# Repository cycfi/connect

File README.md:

# connect
Peripherals for connecting and controlling musical instruments

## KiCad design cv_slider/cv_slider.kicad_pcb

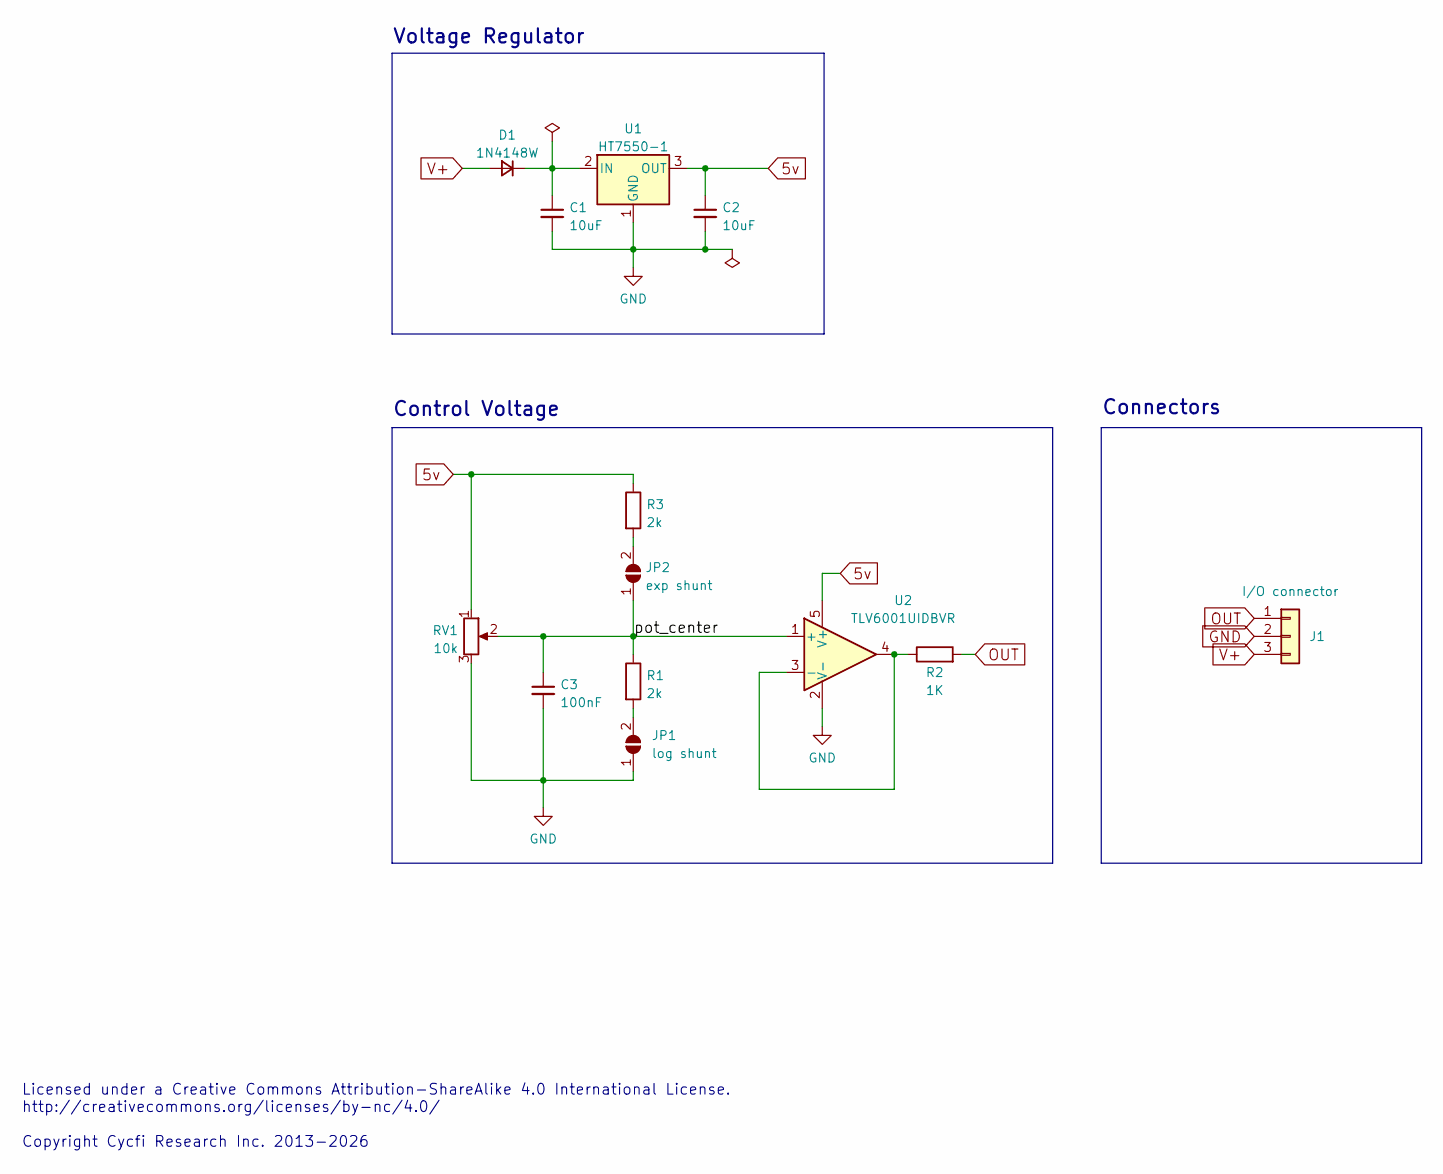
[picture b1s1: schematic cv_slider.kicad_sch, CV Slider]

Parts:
C1, C2: 10uF; C_0805_2012Metric; LCSC C15850
C3: 100nF; C_0402_1005Metric; LCSC C307331
D1: 1N4148W; D_SOD-123; LCSC C81598
J1: I/O connector; pin_header_1x3p_2.54mm_smd_horizontal; LCSC C5242196
JP1: log shunt; SolderJumper-2_P1.3mm_Open_TrianglePad1.0x1.5mm
JP2: exp shunt; SolderJumper-2_P1.3mm_Open_TrianglePad1.0x1.5mm
R1, R3: 2k; R_0402_1005Metric; LCSC C4109
R2: 1K; R_0402_1005Metric; LCSC C11702
RV1: 10k; Alps_RS301111A01G
U1: HT7550-1; SOT-89-3; LCSC C16106
U2: TLV6001UIDBVR; SOT-23-5; LCSC C544299

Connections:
5v: C2.1, R3.1, RV1.1, U1.3 (OUT), U2.5 (V+)
/pot_center: C3.1, JP2.1 (A), R1.1, RV1.2, U2.1 (+)
GND: C1.2, C2.2, C3.2, J1.2, JP1.1 (A), RV1.3, U1.1 (GND), U2.2 (V-)
unnamed: C1.1, D1.1 (K), U1.2 (IN)
unnamed: JP1.2 (B), R1.2
unnamed: JP2.2 (B), R3.2
unnamed: R2.1, U2.3 (-), U2.4
OUT: J1.1, R2.2
V+: D1.2 (A), J1.3

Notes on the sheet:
Control Voltage
Licensed under a Creative Commons Attribution-ShareAlike 4.0 International License. http://creativecommons.org/licenses/by-nc/4.0/ Copyright Cycfi Research Inc. 2013-2026
Voltage Regulator
Connectors

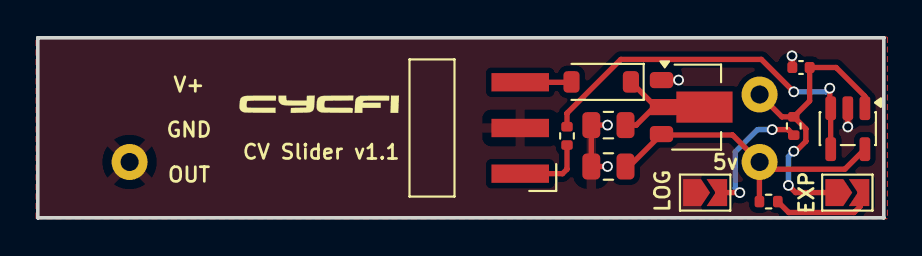
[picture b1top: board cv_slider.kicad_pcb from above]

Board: 2 copper layers, 47.0 x 10.0 mm, 13 parts (1 on the bottom side), 9 nets.

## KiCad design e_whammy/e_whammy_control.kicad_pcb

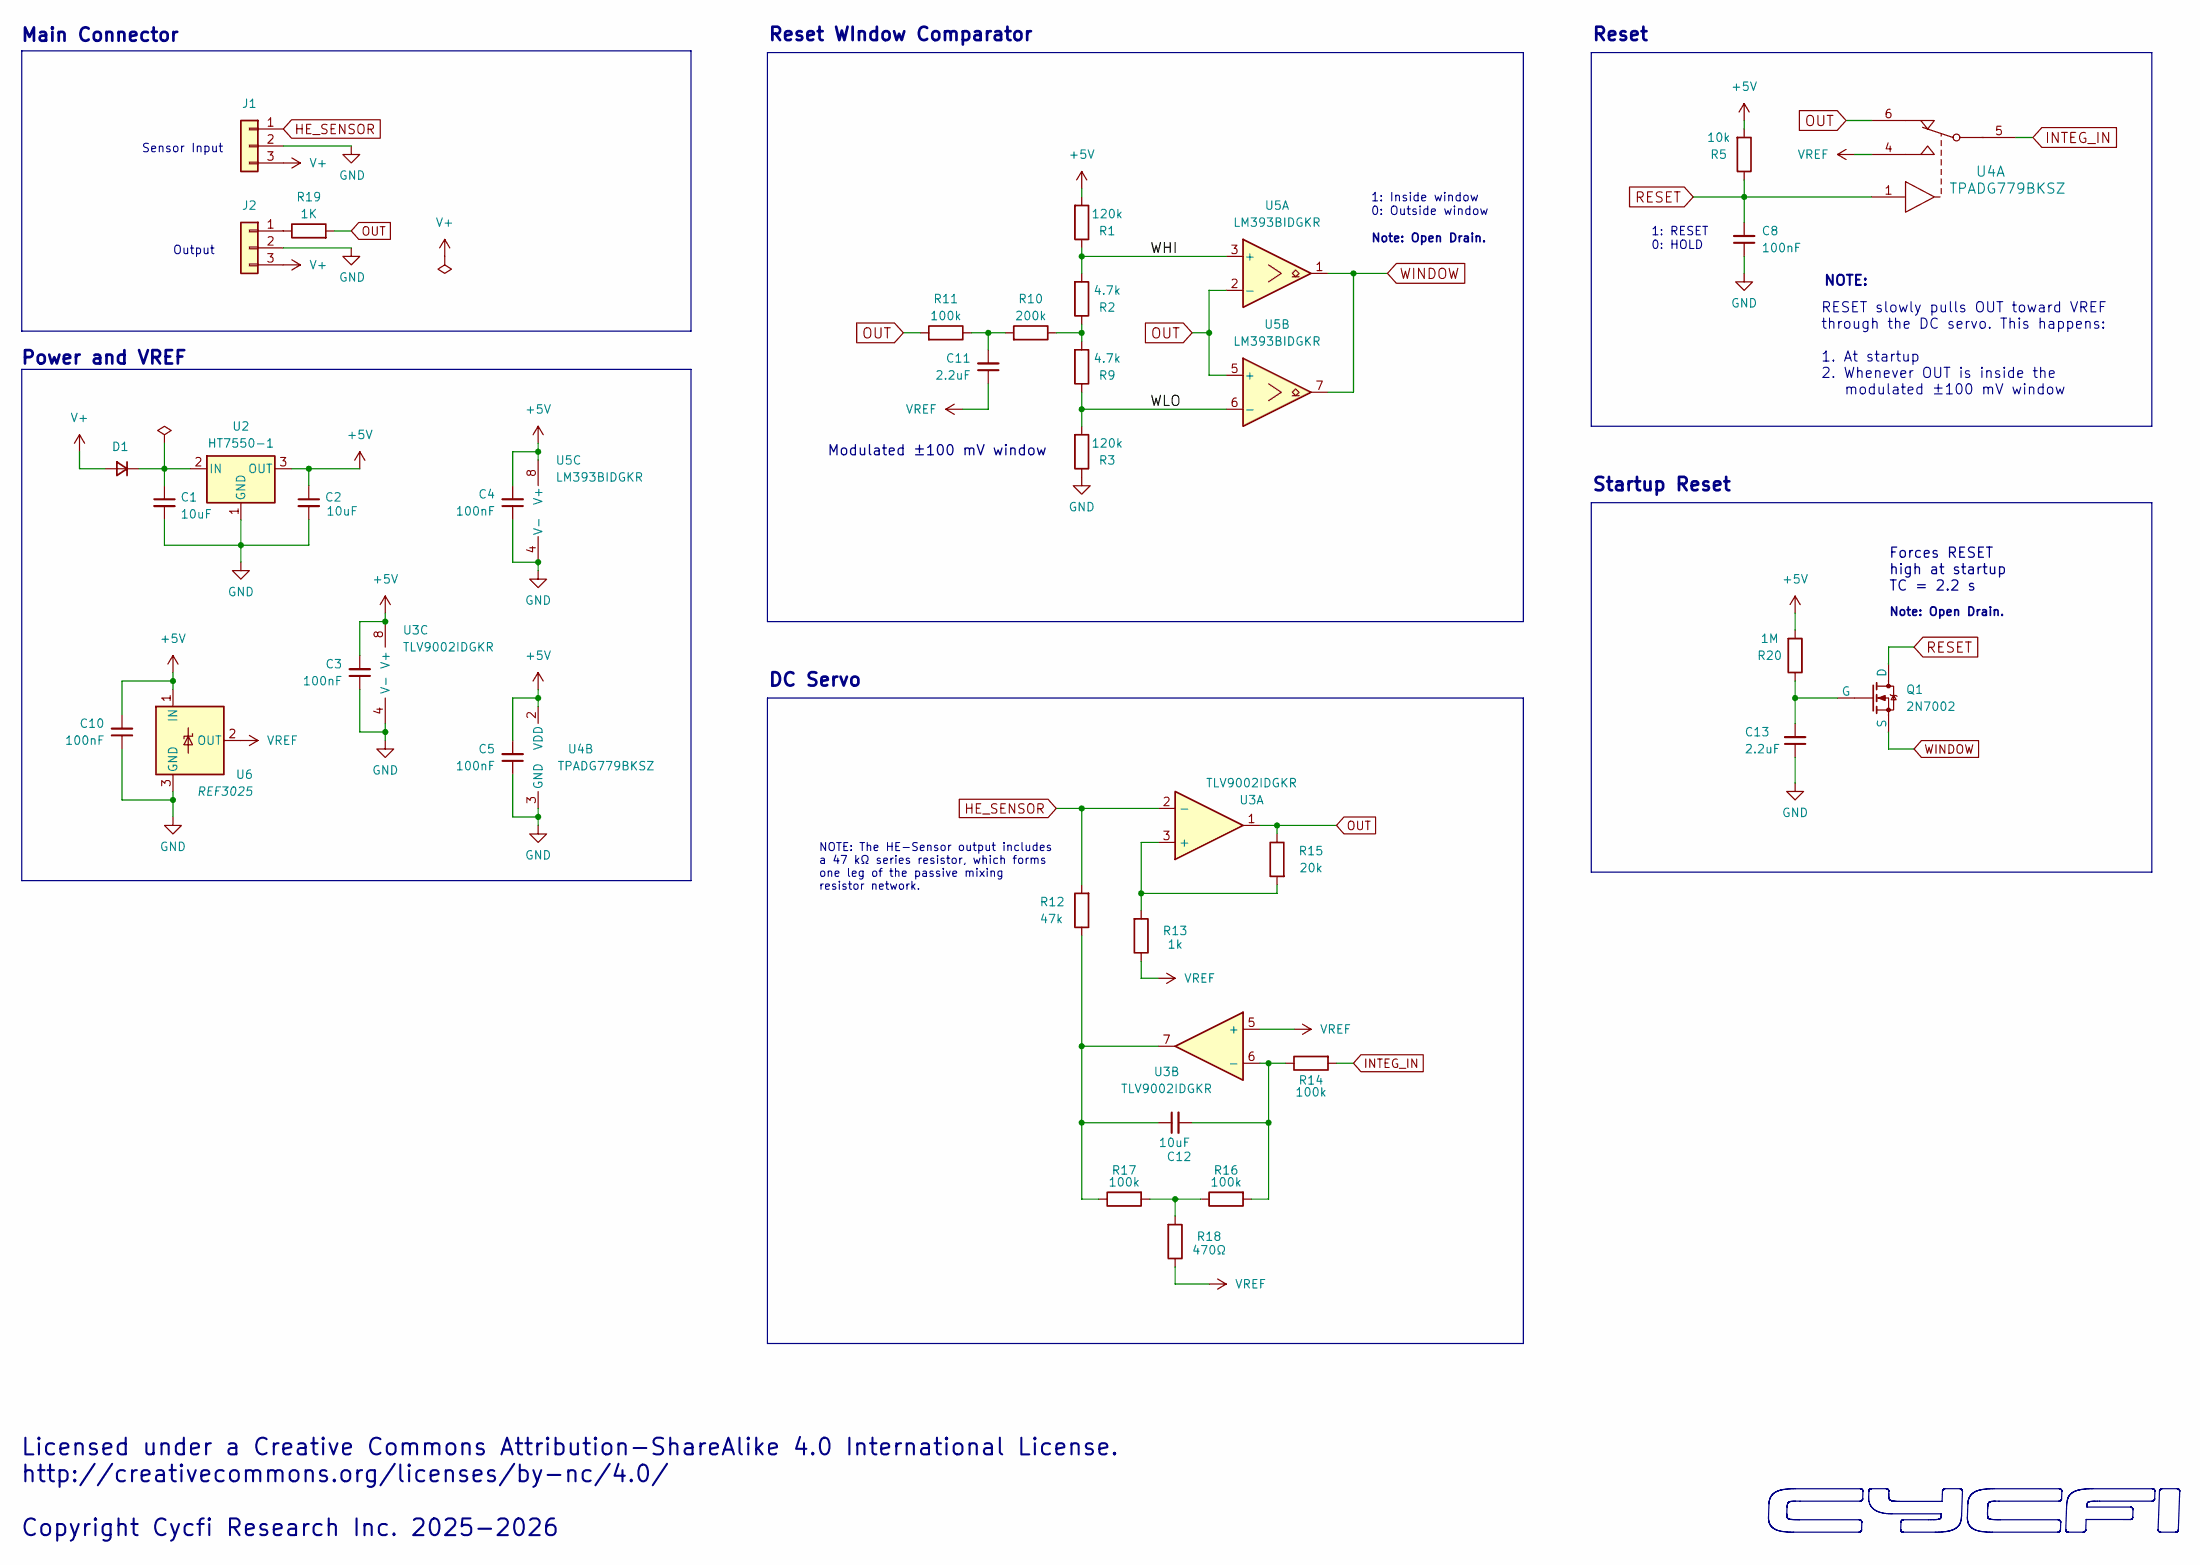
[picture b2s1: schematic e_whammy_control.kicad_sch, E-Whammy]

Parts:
C1, C2: 10uF; C_0603_1608Metric; LCSC C96446
C3, C4, C5, C8, C10: 100nF; C_0402_1005Metric; LCSC C307331
C11, C13: 2.2uF; C_0402_1005Metric; LCSC C72203
C12: 10uF; C_0805_2012Metric; LCSC C95841
D1: 1N4148WS; D_SOD-323; LCSC C2128
J1, J2: Conn_01x03; pin_header_1x3p_2.54mm_smd_horizontal
Q1: 2N7002; SOT-23; LCSC C8545
R1, R3: 120k; R_0402_1005Metric; LCSC C25750
R2, R9: 4.7k; R_0402_1005Metric; LCSC C25900
R5: 10k; R_0402_1005Metric; LCSC C25744
R10: 200k; R_0402_1005Metric; LCSC C25764
R11: 100k; R_0402_1005Metric; LCSC C25741
R12: 47k; R_0402_1005Metric; LCSC C25792
R13: 1k; R_0402_1005Metric; LCSC C11702
R14, R16, R17: 100k; R_0402_1005Metric; LCSC C25530
R15: 20k; R_0402_1005Metric; LCSC C25765
R18: 470Ω; R_0402_1005Metric; LCSC C25117
R19: 1K; R_0402_1005Metric; LCSC C11702
R20: 1M; R_0402_1005Metric; LCSC C26083
U2: HT7550-1; SOT-23-132; LCSC C5379082
U3: TLV9002IDGKR; VSSOP-8_3x3mm_P0.65mm; LCSC C398361
U4: TPADG779BKSZ; KS_6_ADI; LCSC C42449021
U5: LM393BIDGKR; VSSOP-8_3x3mm_P0.65mm; LCSC C3659248
U6: REF3025; SOT-23; LCSC C11334

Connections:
+5V: C2.1, C3.2, C4.2, C5.2, C10.2, R1.2, R5.2, R20.2, U2.3 (OUT), U3.8 (V+), U4.2 (VDD), U5.8 (V+), U6.1 (IN)
/WHI: R1.1, R2.2, U5.3 (+)
/WLO: R3.2, R9.1, U5.6 (-)
GND: C1.2, C2.2, C3.1, C4.1, C5.1, C8.1, C10.1, C13.1, J1.2, J2.2, R3.1, U2.1 (GND), U3.4 (V-), U4.3 (GND), U5.4 (V-), U6.3 (GND)
HE_SENSOR: J1.1, R12.2, U3.2 (-)
INTEG_IN: R14.2, U4.5
unnamed: C11.2, R10.2, R11.1
unnamed: C12.1, R12.1, R17.1, U3.7
unnamed: C1.1, D1.1 (K), U2.2 (IN)
unnamed: J2.1, R19.1
unnamed: C13.2, Q1.1 (G), R20.1
unnamed: R2.1, R9.2, R10.1
unnamed: R16.1, R17.2, R18.2
unnamed: R13.2, R15.2, U3.3 (+)
unnamed: C12.2, R14.1, R16.2, U3.6 (-)
OUT: R11.2, R15.1, R19.2, U3.1, U4.6, U5.2 (-), U5.5 (+)
RESET: C8.2, Q1.3 (D), R5.1, U4.1
V+: D1.2 (A), J1.3, J2.3
VREF: C11.1, R13.1, R18.1, U3.5 (+), U4.4, U6.2 (OUT)
WINDOW: Q1.2 (S), U5.1, U5.7

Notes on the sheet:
Modulated ±100 mV window
NOTE:
Reset
Main Connector
Note: Open Drain.
NOTE: The HE-Sensor output includes a 47 kΩ series resistor, which forms one leg of the passive mixing resistor network.
Sensor Input
DC Servo
RESET slowly pulls OUT toward VREF through the DC servo. This happens: 1. At startup 2. Whenever OUT is inside the modulated ±100 mV window
1: RESET 0: HOLD
Output
Reset WIndow Comparator
Startup Reset
Licensed under a Creative Commons Attribution-ShareAlike 4.0 International License. http://creativecommons.org/licenses/by-nc/4.0/ Copyright Cycfi Research Inc. 2025-2026
Forces RESET high at startup TC = 2.2 s
1: Inside window 0: Outside window
Power and VREF

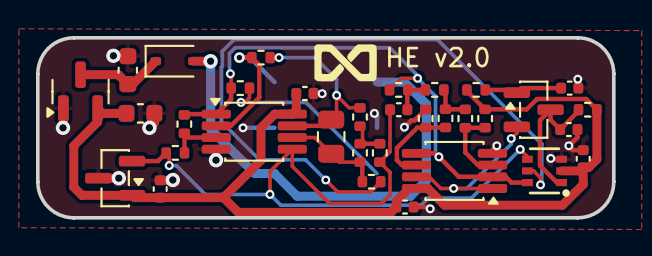
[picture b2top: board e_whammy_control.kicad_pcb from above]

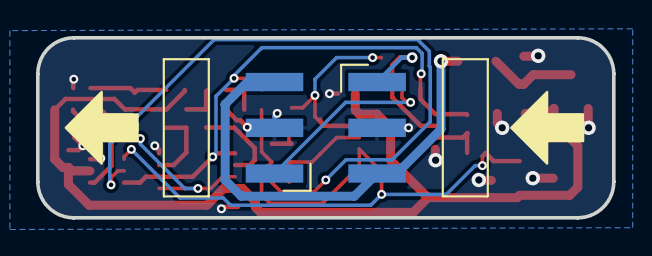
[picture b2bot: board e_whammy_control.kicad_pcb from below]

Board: 2 copper layers, 32.0 x 10.0 mm, 35 parts (2 on the bottom side), 20 nets.

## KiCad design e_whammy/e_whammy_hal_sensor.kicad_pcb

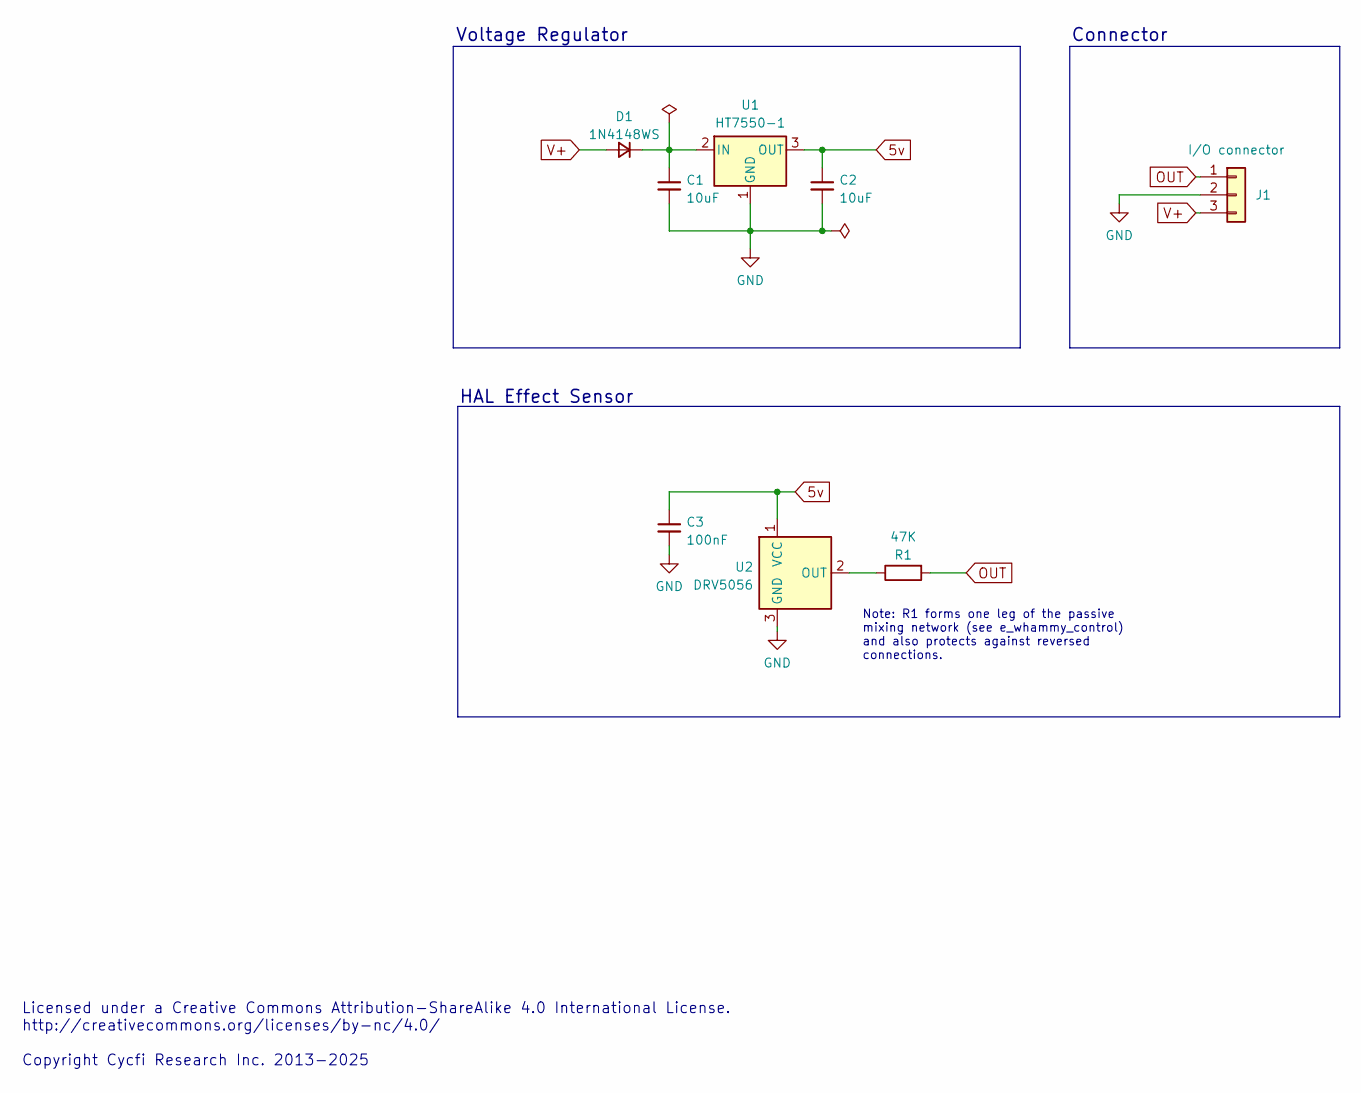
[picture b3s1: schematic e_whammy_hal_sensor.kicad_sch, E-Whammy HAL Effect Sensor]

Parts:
C1, C2: 10uF; C_0603_1608Metric; LCSC C96446
C3: 100nF; C_0402_1005Metric; LCSC C307331
D1: 1N4148WS; D_SOD-323; LCSC C2128
J1: I/O connector; PinHeader_1x03_P2.54mm_Vertical; LCSC C6332196
R1: 47K; R_0402_1005Metric; LCSC C25792
U1: HT7550-1; SOT-23-132; LCSC C5379082
U2: DRV5056; SOT-23; LCSC C2866615

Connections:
5v: C2.1, C3.1, U1.3 (OUT), U2.1 (VCC)
GND: C1.2, C2.2, C3.2, J1.2, U1.1 (GND), U2.3 (GND)
unnamed: C1.1, D1.1 (K), U1.2 (IN)
unnamed: R1.1, U2.2 (OUT)
OUT: J1.1, R1.2
V+: D1.2 (A), J1.3

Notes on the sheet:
Note: R1 forms one leg of the passive mixing network (see e_whammy_control) and also protects against reversed connections.
Connector
Licensed under a Creative Commons Attribution-ShareAlike 4.0 International License. http://creativecommons.org/licenses/by-nc/4.0/ Copyright Cycfi Research Inc. 2013-2025
Voltage Regulator
HAL Effect Sensor

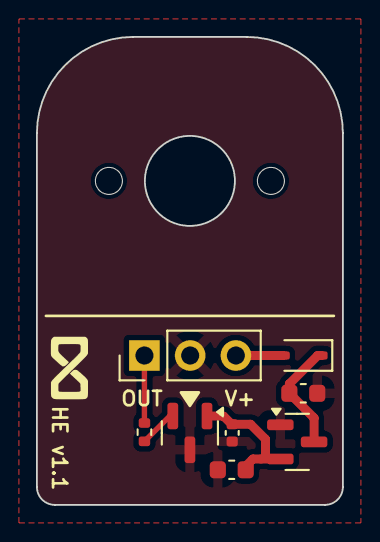
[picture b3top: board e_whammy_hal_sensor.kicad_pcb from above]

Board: 2 copper layers, 17.0 x 26.0 mm, 8 parts (0 on the bottom side), 6 nets.

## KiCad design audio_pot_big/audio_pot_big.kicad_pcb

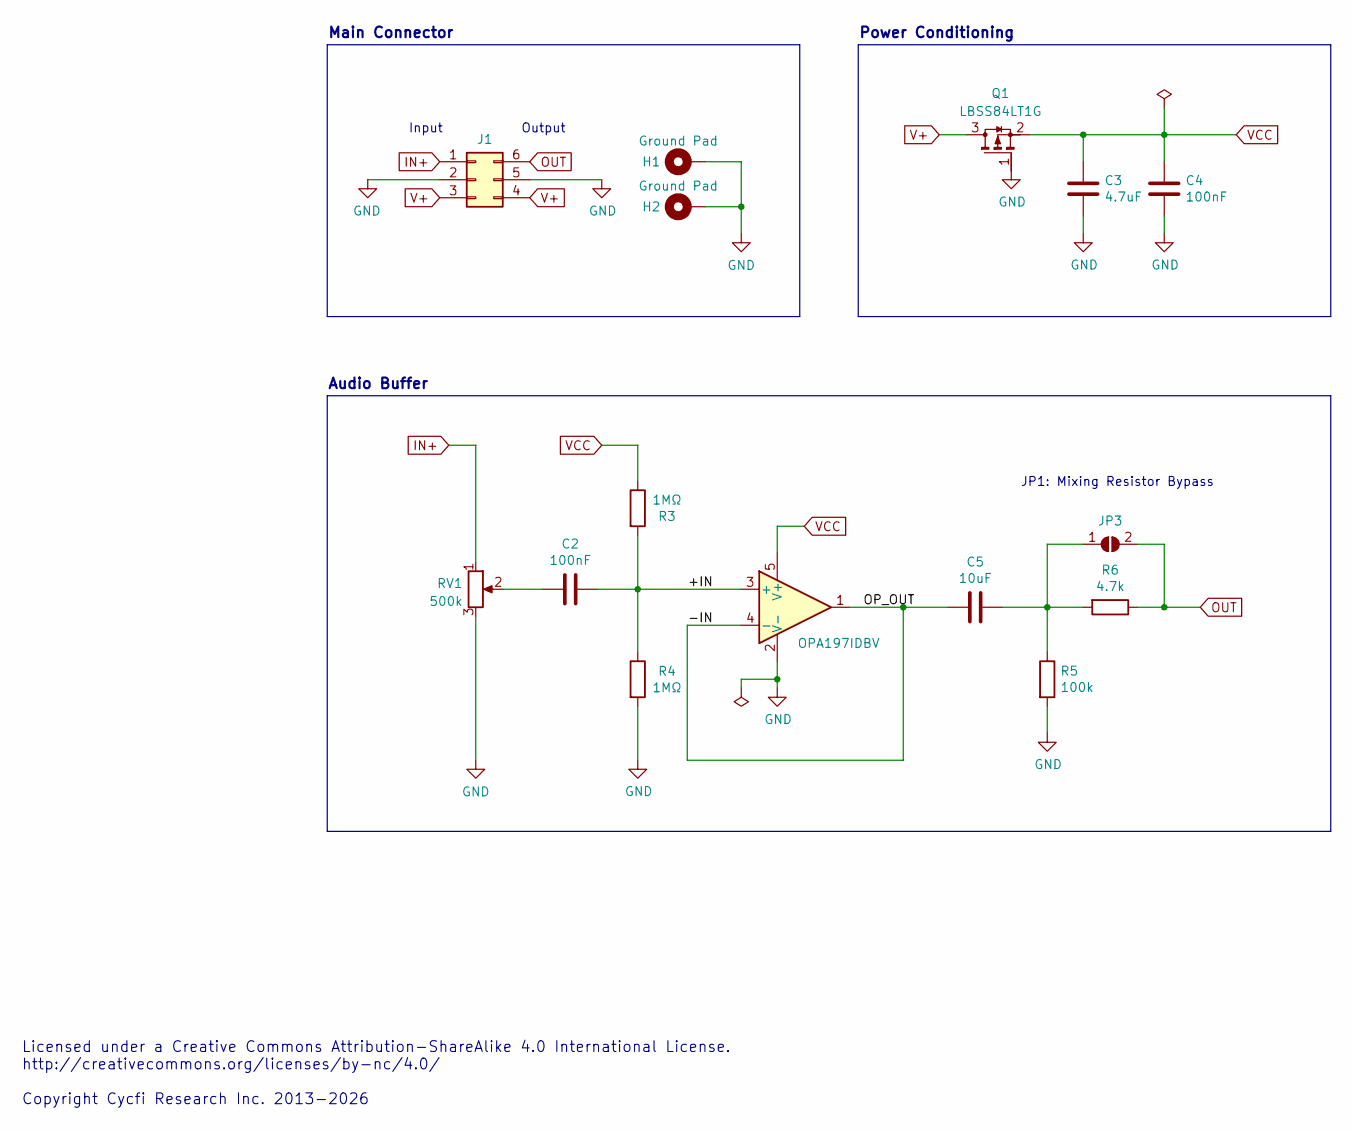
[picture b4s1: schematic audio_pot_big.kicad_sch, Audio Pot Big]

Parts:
C2: 100nF; C_0805_2012Metric; LCSC C49678
C3: 4.7uF; C_0805_2012Metric; LCSC C1779
C4: 100nF; C_0402_1005Metric; LCSC C307331
C5: 10uF; C_0805_2012Metric; LCSC C15850
H1, H2: Ground Pad; single-pad-2x2-circular
J1: Conn_02x03_Counter_Clockwise; pin_header_2x3p_2.54mm_smd_horizontal; LCSC C46061685
JP3: SolderJumper_2_Open; SolderJumper-2_P1.3mm_Open_TrianglePad1.0x1.5mm
Q1: LBSS84LT1G; TSOT-23; LCSC C8492
R3, R4: 1MΩ; R_0402_1005Metric; LCSC C26083
R5: 100k; R_0402_1005Metric; LCSC C25741
R6: 4.7k; R_0402_1005Metric; LCSC C25900
RV1: 500k; bourns_pdb241
U1: OPA197IDBV; SOT-23-5; LCSC C131929

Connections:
/+IN: C2.1, R3.2, R4.1, U1.3 (+)
/-IN: C5.2, U1.1, U1.4 (-)
GND: C3.2, C4.2, H1.1, H2.1, J1.2, J1.5, Q1.1 (G), R4.2, R5.2, RV1.3, U1.2 (V-)
IN+: J1.1, RV1.1
unnamed: C2.2, RV1.2
unnamed: C5.1, JP3.1 (A), R5.1, R6.2
OUT: J1.6, JP3.2 (B), R6.1
V+: J1.3, J1.4, Q1.3 (D)
VCC: C3.1, C4.1, Q1.2 (S), R3.1, U1.5 (V+)

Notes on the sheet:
Power Conditioning
JP1: Mixing Resistor Bypass
Input
Licensed under a Creative Commons Attribution-ShareAlike 4.0 International License. http://creativecommons.org/licenses/by-nc/4.0/ Copyright Cycfi Research Inc. 2013-2026
Output
Main Connector
Audio Buffer

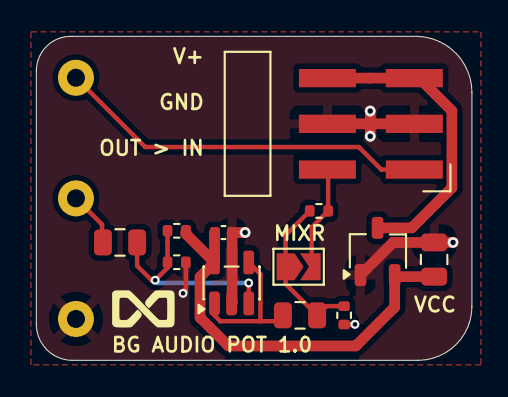
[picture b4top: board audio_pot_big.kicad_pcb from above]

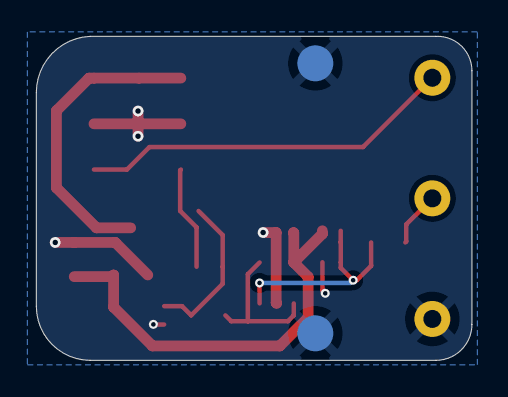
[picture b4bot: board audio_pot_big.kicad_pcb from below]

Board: 2 copper layers, 24.2 x 18.0 mm, 15 parts (2 on the bottom side), 9 nets.

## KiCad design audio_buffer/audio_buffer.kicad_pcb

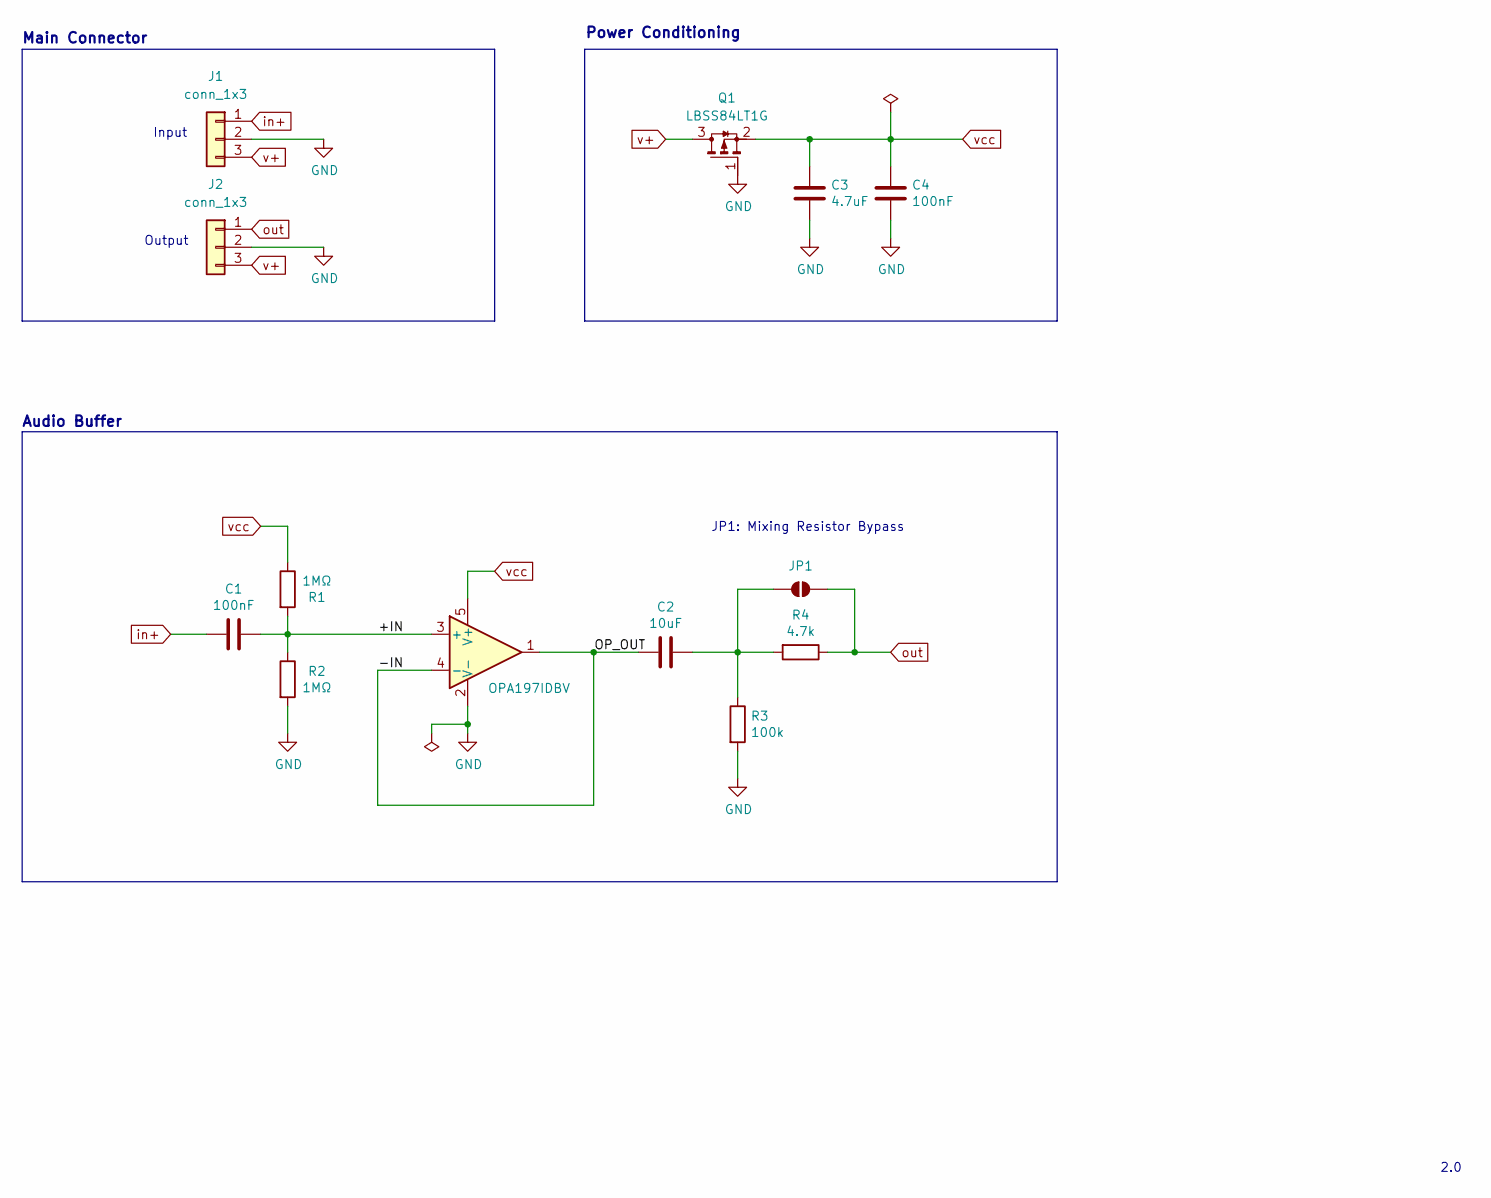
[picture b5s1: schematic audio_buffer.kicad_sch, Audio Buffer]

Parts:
C1: 100nF; C_0805_2012Metric; LCSC C49678
C2: 10uF; C_0805_2012Metric; LCSC C15850
C3: 4.7uF; C_0805_2012Metric; LCSC C1779
C4: 100nF; C_0402_1005Metric; LCSC C307331
J1, J2: conn_1x3; pin_header_1x3p_2.54mm_smd_horizontal
JP1: SolderJumper_2_Open; SolderJumper-2_P1.3mm_Open_TrianglePad1.0x1.5mm
Q1: LBSS84LT1G; TSOT-23; LCSC C8492
R1, R2: 1MΩ; R_0402_1005Metric; LCSC C26083
R3: 100k; R_0402_1005Metric; LCSC C25741
R4: 4.7k; R_0402_1005Metric; LCSC C25900
U1: OPA197IDBV; SOT-23-5; LCSC C131929

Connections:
/+IN: C1.1, R1.2, R2.1, U1.3 (+)
/-IN: C2.2, U1.1, U1.4 (-)
GND: C3.2, C4.2, J1.2, J2.2, Q1.1 (G), R2.2, R3.2, U1.2 (V-)
unnamed: C2.1, JP1.1 (A), R3.1, R4.2
in+: C1.2, J1.1
out: J2.1, JP1.2 (B), R4.1
v+: J1.3, J2.3, Q1.3 (D)
vcc: C3.1, C4.1, Q1.2 (S), R1.1, U1.5 (V+)

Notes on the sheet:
Power Conditioning
Input
JP1: Mixing Resistor Bypass
2.0
Output
Audio Buffer
Main Connector

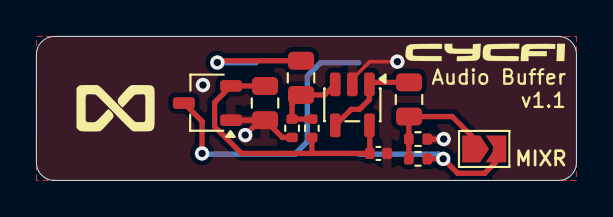
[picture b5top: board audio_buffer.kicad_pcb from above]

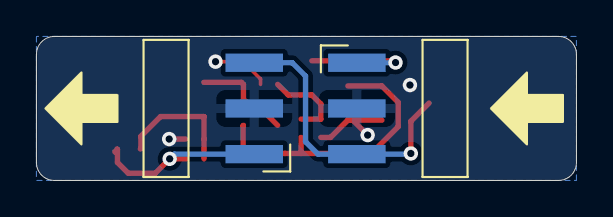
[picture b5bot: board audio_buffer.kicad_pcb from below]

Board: 2 copper layers, 30.0 x 8.0 mm, 13 parts (2 on the bottom side), 8 nets.

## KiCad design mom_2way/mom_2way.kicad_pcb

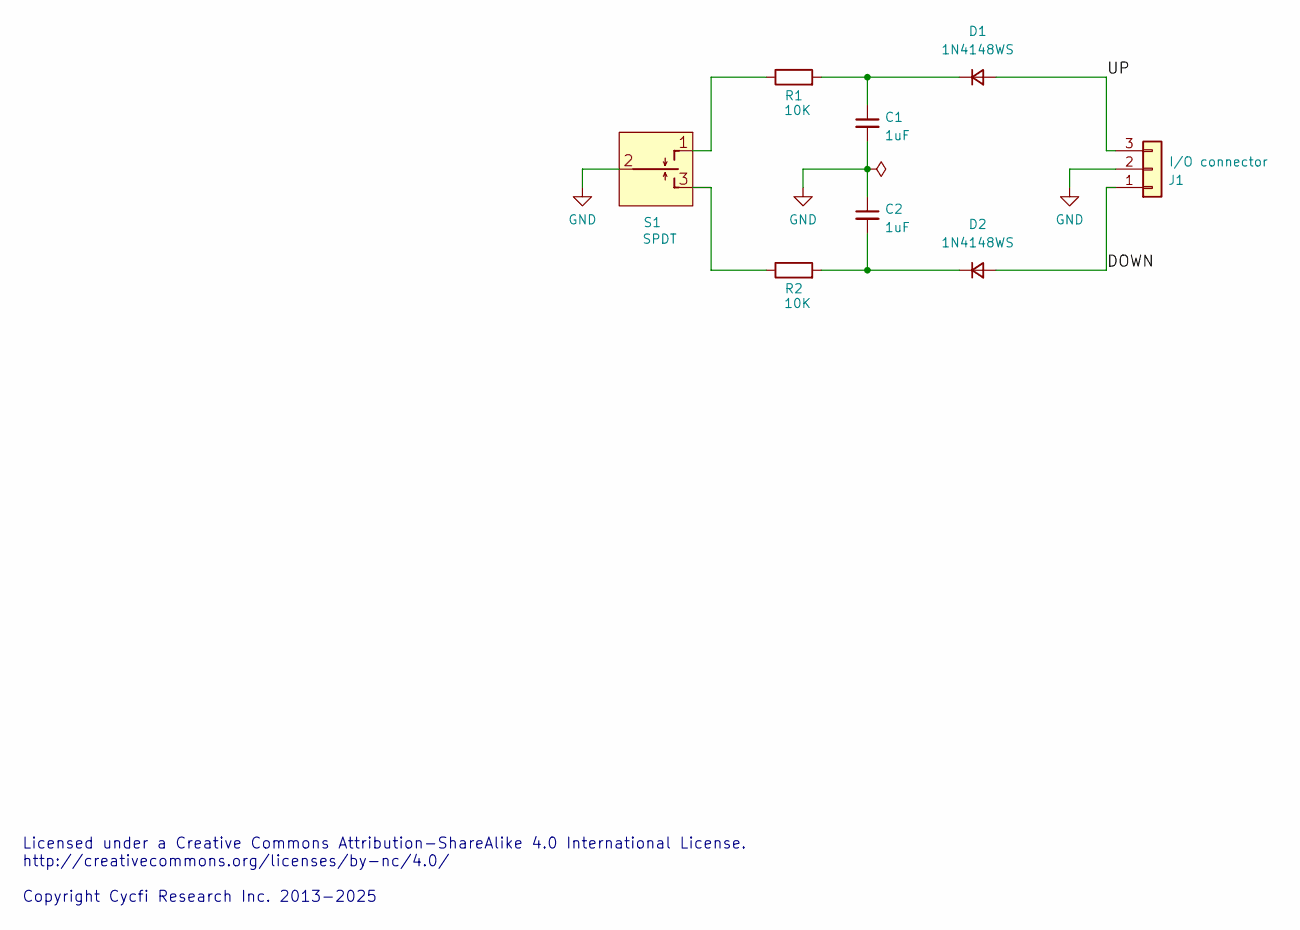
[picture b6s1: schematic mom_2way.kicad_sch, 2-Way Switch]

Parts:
C1, C2: 1uF; C_0603_1608Metric; LCSC C15849
D1, D2: 1N4148WS; D_SOD-323; LCSC C2128
J1: I/O connector; pin_header_1x3p_2.54mm_smd_horizontal; LCSC C6332196
R1, R2: 10K; R_0402_1005Metric; LCSC C25744
S1: SPDT; MINI_SPDT

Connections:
/DOWN: D2.2 (A), J1.1
/UP: D1.2 (A), J1.3
GND: C1.2, C2.1, J1.2, S1.2
unnamed: C1.1, D1.1 (K), R1.2
unnamed: C2.2, D2.1 (K), R2.2
unnamed: R1.1, S1.1 (O)
unnamed: R2.1, S1.3 (S)

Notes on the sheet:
Licensed under a Creative Commons Attribution-ShareAlike 4.0 International License. http://creativecommons.org/licenses/by-nc/4.0/ Copyright Cycfi Research Inc. 2013-2025

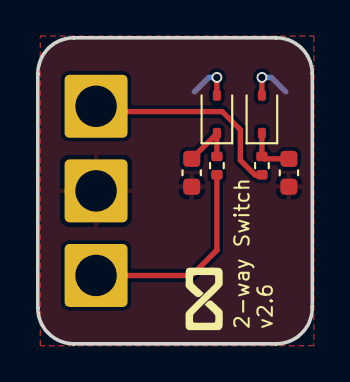
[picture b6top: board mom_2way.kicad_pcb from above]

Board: 2 copper layers, 15.2 x 17.0 mm, 8 parts (1 on the bottom side), 7 nets.

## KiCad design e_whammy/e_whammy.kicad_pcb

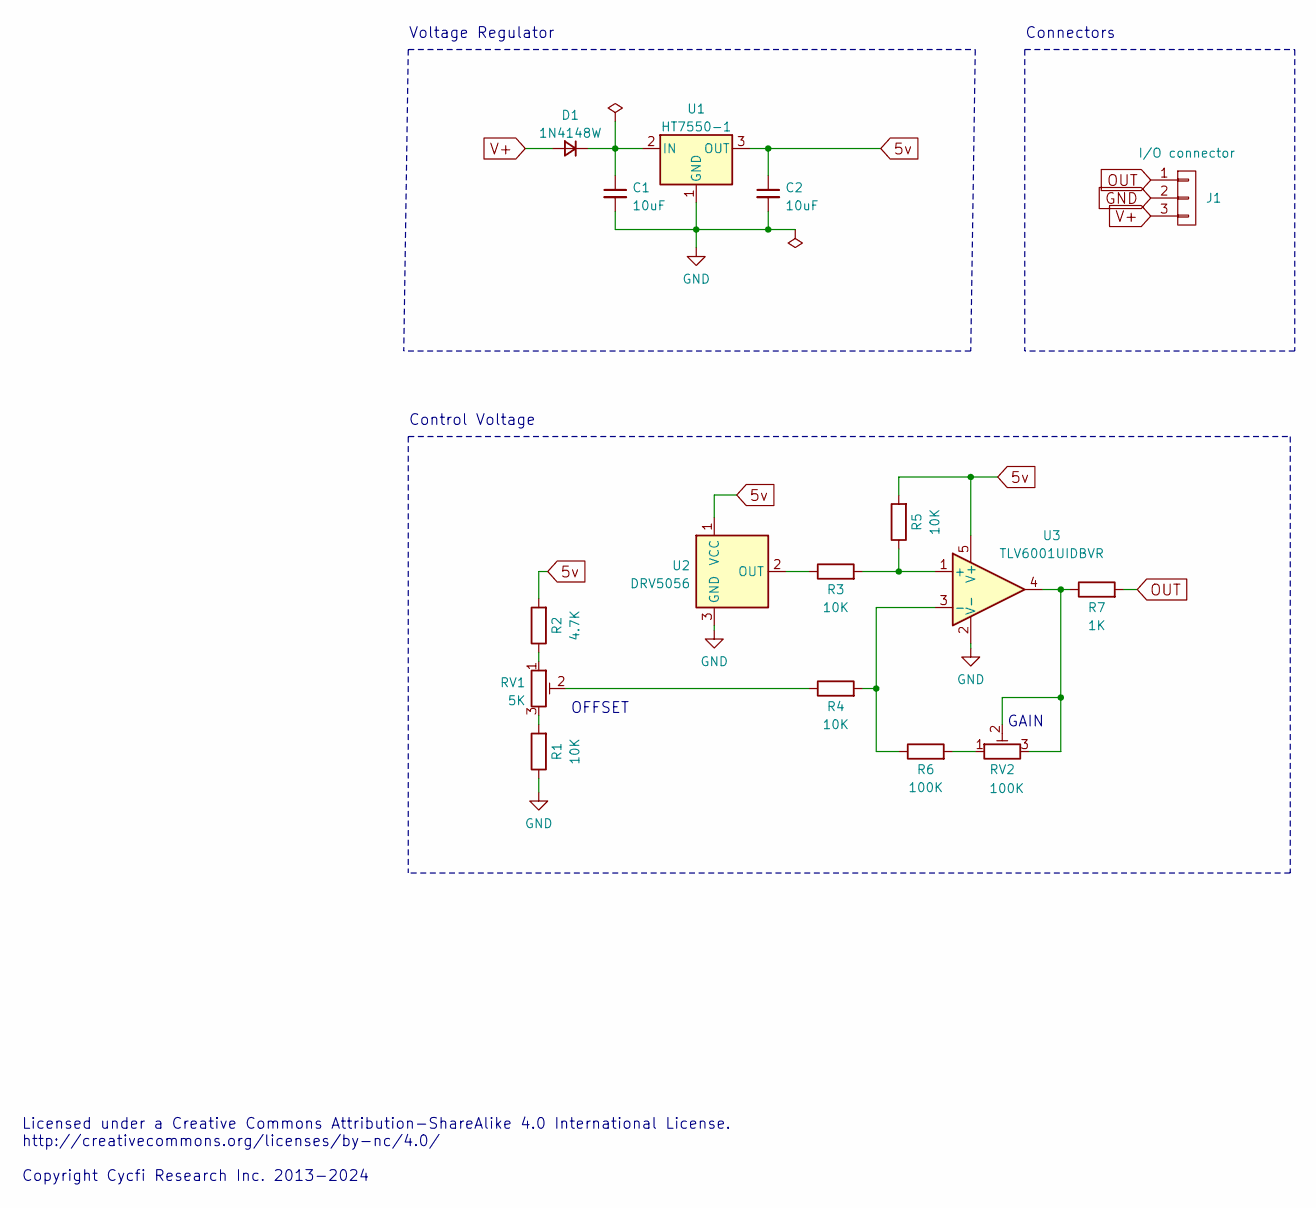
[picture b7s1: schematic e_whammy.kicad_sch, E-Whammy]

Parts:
C1, C2: 10uF; C_0805_2012Metric; LCSC C15850
D1: 1N4148W; D_SOD-123; LCSC C81598
J1: I/O connector; PinHeader_1x03_P2.54mm_Vertical; LCSC C6332196
R1, R3, R4, R5: 10K; R_0402_1005Metric; LCSC C25744
R2: 4.7K; R_0402_1005Metric; LCSC C25900
R6: 100K; R_0402_1005Metric; LCSC C25741
R7: 1K; R_0402_1005Metric; LCSC C11702
RV1: 5K; TC33X-2; LCSC C719177
RV2: 100K; TC33X-2; LCSC C719186
U1: HT7550-1; SOT-89-3; LCSC C16106
U2: DRV5056; SOT-23; LCSC C2866615
U3: TLV6001UIDBVR; SOT-23-5; LCSC C544299

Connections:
5v: C2.1, R2.2, R5.2, U1.3 (OUT), U2.1 (VCC), U3.5 (V+)
GND: C1.2, C2.2, J1.2, R1.1, U1.1 (GND), U2.3 (GND), U3.2 (V-)
unnamed: C1.1, D1.1 (K), U1.2 (IN)
unnamed: R1.2, RV1.3
unnamed: R2.1, RV1.1
unnamed: R4.1, RV1.2
unnamed: R6.2, RV2.1
unnamed: R7.1, RV2.2, RV2.3, U3.4
unnamed: R3.1, U2.2 (OUT)
unnamed: R3.2, R5.1, U3.1 (+)
unnamed: R4.2, R6.1, U3.3 (-)
OUT: J1.1, R7.2
V+: D1.2 (A), J1.3

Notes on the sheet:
Connectors
GAIN
OFFSET
Licensed under a Creative Commons Attribution-ShareAlike 4.0 International License. http://creativecommons.org/licenses/by-nc/4.0/ Copyright Cycfi Research Inc. 2013-2024
Voltage Regulator
Control Voltage

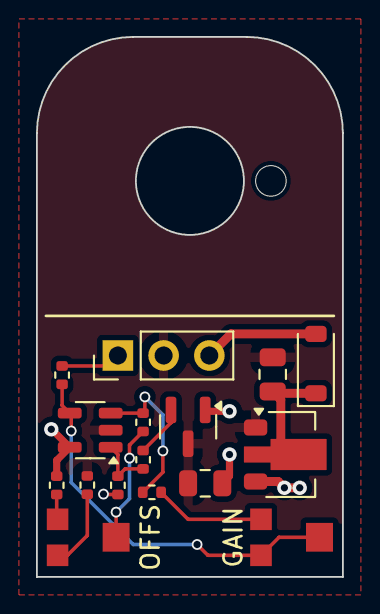
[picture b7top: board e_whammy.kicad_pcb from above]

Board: 4 copper layers, 17.0 x 30.0 mm, 16 parts (0 on the bottom side), 13 nets.

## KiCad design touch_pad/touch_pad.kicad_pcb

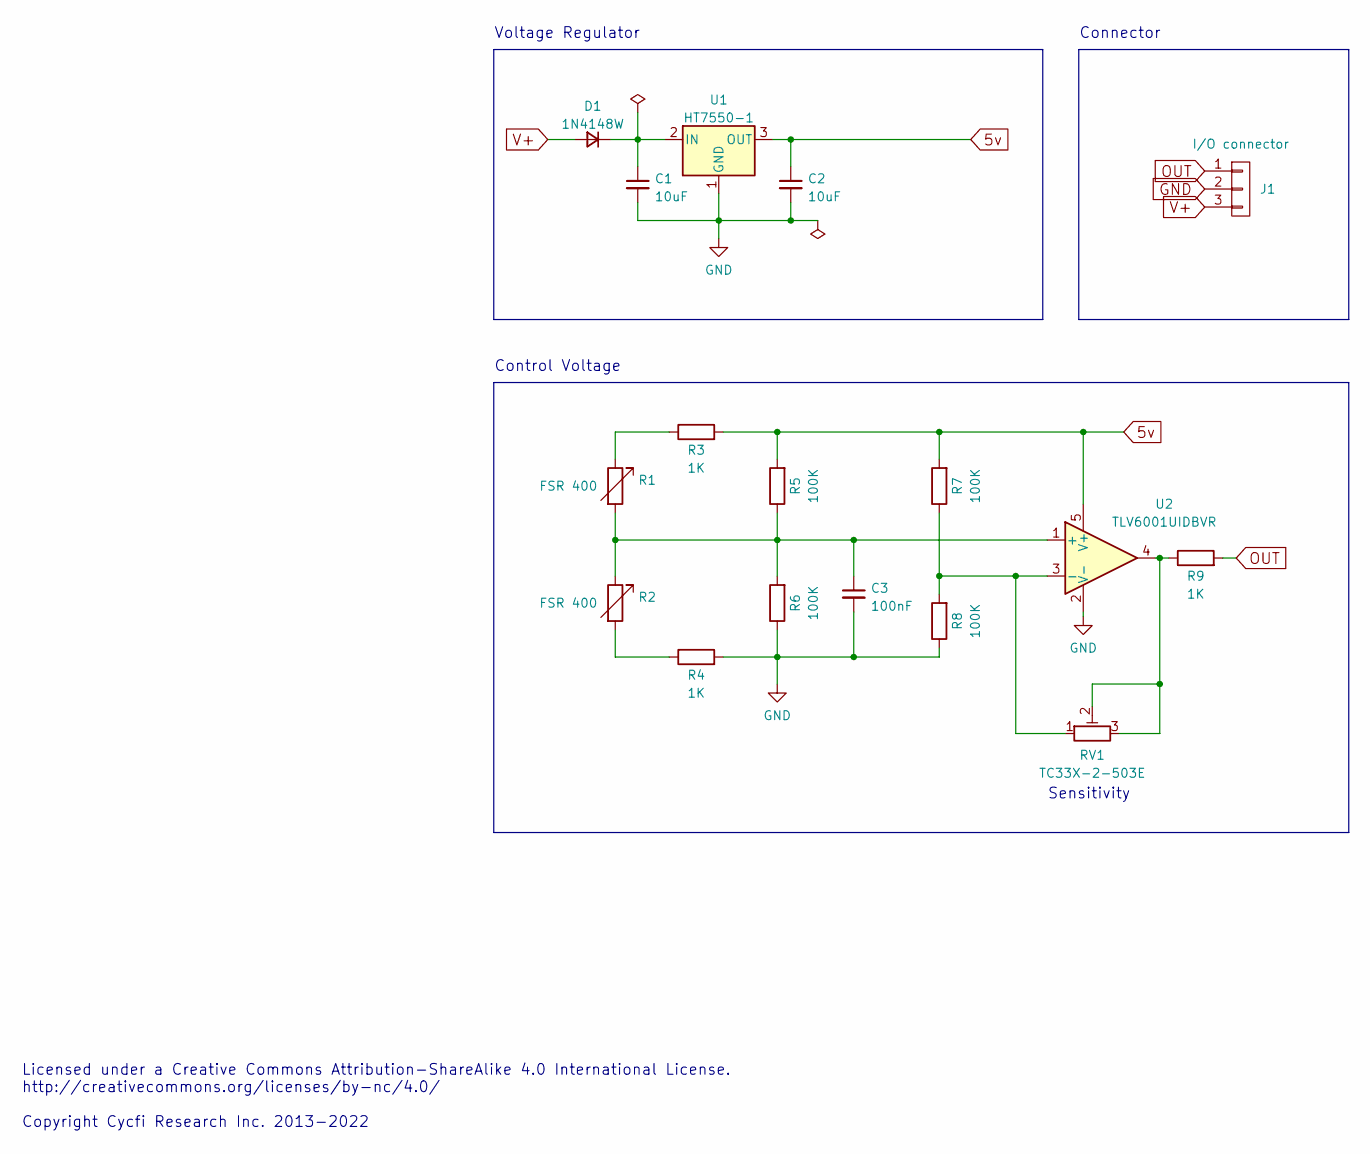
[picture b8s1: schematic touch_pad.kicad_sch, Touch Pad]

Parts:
C1, C2: 10uF; C_0805_2012Metric; LCSC C15850
C3: 100nF; C_0402_1005Metric; LCSC C307331
D1: 1N4148W; D_SOD-123; LCSC C81598
J1: I/O connector; PinHeader_1x03_P2.54mm_Vertical_SMD_Pin1Left; LCSC C2883760
R1, R2: FSR 400; FSR-400
R3, R4, R9: 1K; R_0402_1005Metric; LCSC C11702
R5, R6, R7, R8: 100K; R_0402_1005Metric; LCSC C25741
RV1: TC33X-2-503E; TC33X-2; LCSC C913246
U1: HT7550-1; SOT-89-3; LCSC C16106
U2: TLV6001UIDBVR; SOT-23-5; LCSC C544299

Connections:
5v: C2.1, R3.2, R5.2, R7.2, U1.3 (OUT), U2.5 (V+)
GND: C1.2, C2.2, C3.2, J1.2, R4.2, R6.1, R8.1, U1.1 (GND), U2.2 (V-)
unnamed: C1.1, D1.1 (K), U1.2 (IN)
unnamed: C3.1, R1.2, R2.1, R5.1, R6.2, U2.1 (+)
unnamed: R1.1, R3.1
unnamed: R2.2, R4.1
unnamed: R7.1, R8.2, RV1.1, U2.3 (-)
unnamed: R9.1, RV1.2, RV1.3, U2.4
OUT: J1.1, R9.2
V+: D1.2 (A), J1.3

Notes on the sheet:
Connector
Sensitivity
Licensed under a Creative Commons Attribution-ShareAlike 4.0 International License. http://creativecommons.org/licenses/by-nc/4.0/ Copyright Cycfi Research Inc. 2013-2022
Voltage Regulator
Control Voltage

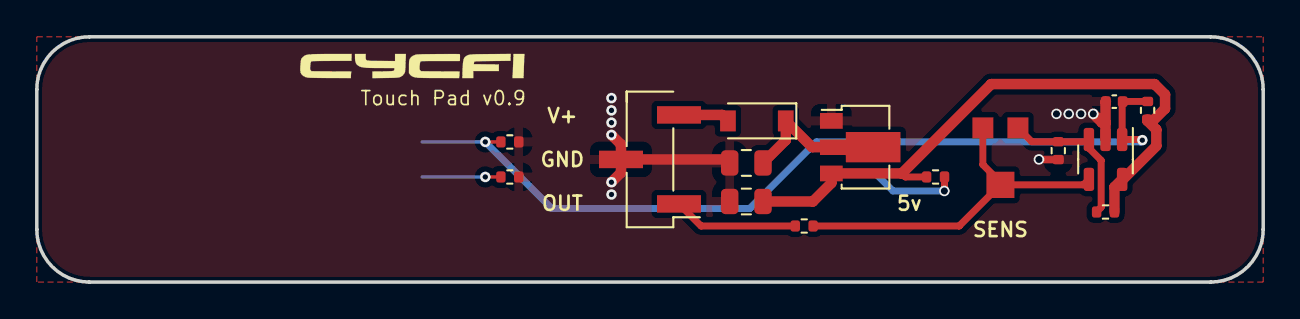
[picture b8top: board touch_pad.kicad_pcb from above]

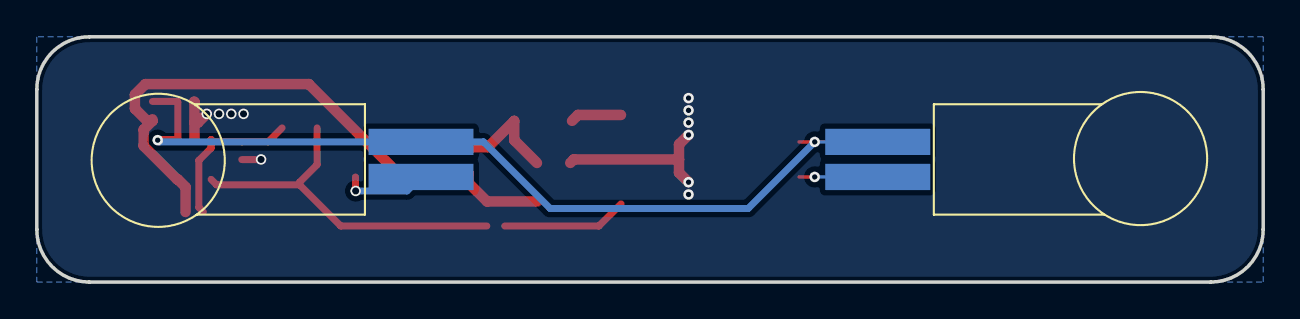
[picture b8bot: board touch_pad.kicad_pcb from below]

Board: 2 copper layers, 70.0 x 14.0 mm, 17 parts (2 on the bottom side), 10 nets.
